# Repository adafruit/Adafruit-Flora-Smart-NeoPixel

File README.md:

# PCB for the Adafruit Flora Smart NeoPixels

<a href="http://www.adafruit.com/products/1060"><br/>Click here to purchase one from the Adafruit shop</a>

__Format is EagleCAD schematic and board layout__

What's a wearable project without LEDs? Our favorite part of the Flora platform is these tiny smart pixels. Designed specifically for wearables, [we found the brightest RGB LEDs available (an eye-blistering ~3800mcd)](http://adafruit.com/products/619) and paired them with a constant-current driver chip that sits on the back. The pixels are chainable - so you only need 1 pin/wire to control as many LEDs as you like. They're easy to sew, and the chainable design means no crossed threads.

__This is the first/original version of the Flora NeoPixels, which runs at at 'low speed' 400KHz communication.__ Unfortunately they are not forward-compatible with [the fully-integrated 'high speed' (800KHz) Flora NeoPixel V2's](http://www.adafruit.com/products/1260). If you have a project that already uses high speed pixels, and you want to attach more pixels to the chain, [you will need to purchase version 2's](http://www.adafruit.com/products/1260) as these are not cross-compatible. __If you don't have any pixels in your project yet, [we suggest purchasing v2 pixels](http://www.adafruit.com/products/1260) as they are lower cost and v1's will eventually be discontinued.__

These pixels have full 24-bit color ability with PWM taken care of by the controller chip. Since the LED is so bright, you need less current/power to get the effects you want. The driver is constant current so its OK if your battery power changes or fluctuates a little.

Each pixel draws as much as 60mA (all three RGB LEDs on for full brightness white). In theory, the Flora can drive up to 500 pixels at 30 FPS (it will run out of RAM after that). However, after about 10 pixels (or if the distance between pixels is more than an inch or two) the resistance of the thread can affect the power supply. For large quantities of pixels over 10, you may want to consider using stranded core wire or copper braid to provide a "power bus" for the pixels - the current draw will add up fast!

Each order comes with 4 individually controllable pixels.

## License
Adafruit invests time and resources providing this open source design,
please support Adafruit and open-source hardware by purchasing
products from Adafruit!

Designed by Adafruit Industries.
Creative Commons Attribution, Share-Alike license, check license.txt for more information
All text above must be included in any redistribution

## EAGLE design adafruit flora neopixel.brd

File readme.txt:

This is the PCB for the Adafruit Flora Smart NeoPixels
Format is EagleCAD schematic and board layout

For more details, check out the product page at

-----> http://adafruit.com/products/1060

Adafruit invests time and resources providing this open source design,
please support Adafruit and open-source hardware by purchasing
products from Adafruit!

Designed by Adafruit Industries.
Creative Commons Attribution, Share-Alike license, check license.txt for more information
All text above must be included in any redistribution

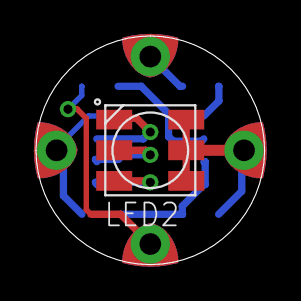
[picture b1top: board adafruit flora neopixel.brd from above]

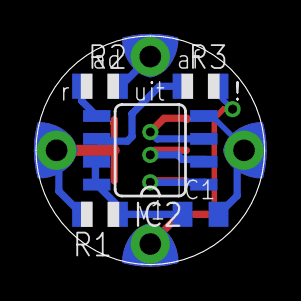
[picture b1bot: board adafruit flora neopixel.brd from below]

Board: 2 copper layers, 12.7 x 12.7 mm, 10 parts (5 on the bottom side), 10 nets.

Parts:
C1: 1uF; C0805K
DATA_INPUT: SEWTAP0.5IN; SEWINGTAP_0.5
DATA_OUTPUT: SEWTAP0.5IN; SEWINGTAP_0.5
GND: SEWTAP0.5IN; SEWINGTAP_0.5
IC2: WS2811-SOP8; SO08-SKINNYPADS
LED2: RGBLED5050
R1: 1.0K; R0805
R2, R3: 22; R0805
VDD: SEWTAP0.5IN; SEWINGTAP_0.5

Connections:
GND: C1.2, GND.TAP, IC2.4
unnamed: IC2.3, LED2.4
unnamed: IC2.2, LED2.5
unnamed: IC2.1, LED2.6
unnamed: IC2.6, R3.1
unnamed: IC2.5, R2.1
unnamed: DATA_INPUT.TAP, R3.2
unnamed: DATA_OUTPUT.TAP, R2.2
unnamed: C1.1, IC2.7, IC2.8, R1.1
VDD: LED2.1, LED2.2, LED2.3, R1.2, VDD.TAP

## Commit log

2013-01-14 whee
2019-04-18 readme + new image
2019-04-18 added license text
